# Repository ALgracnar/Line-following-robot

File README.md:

# Line-following-robot

Rečeno, storjeno. GitHub acount ustvarjen in KiCad naložen.
Lp, Aljaž Gračnar

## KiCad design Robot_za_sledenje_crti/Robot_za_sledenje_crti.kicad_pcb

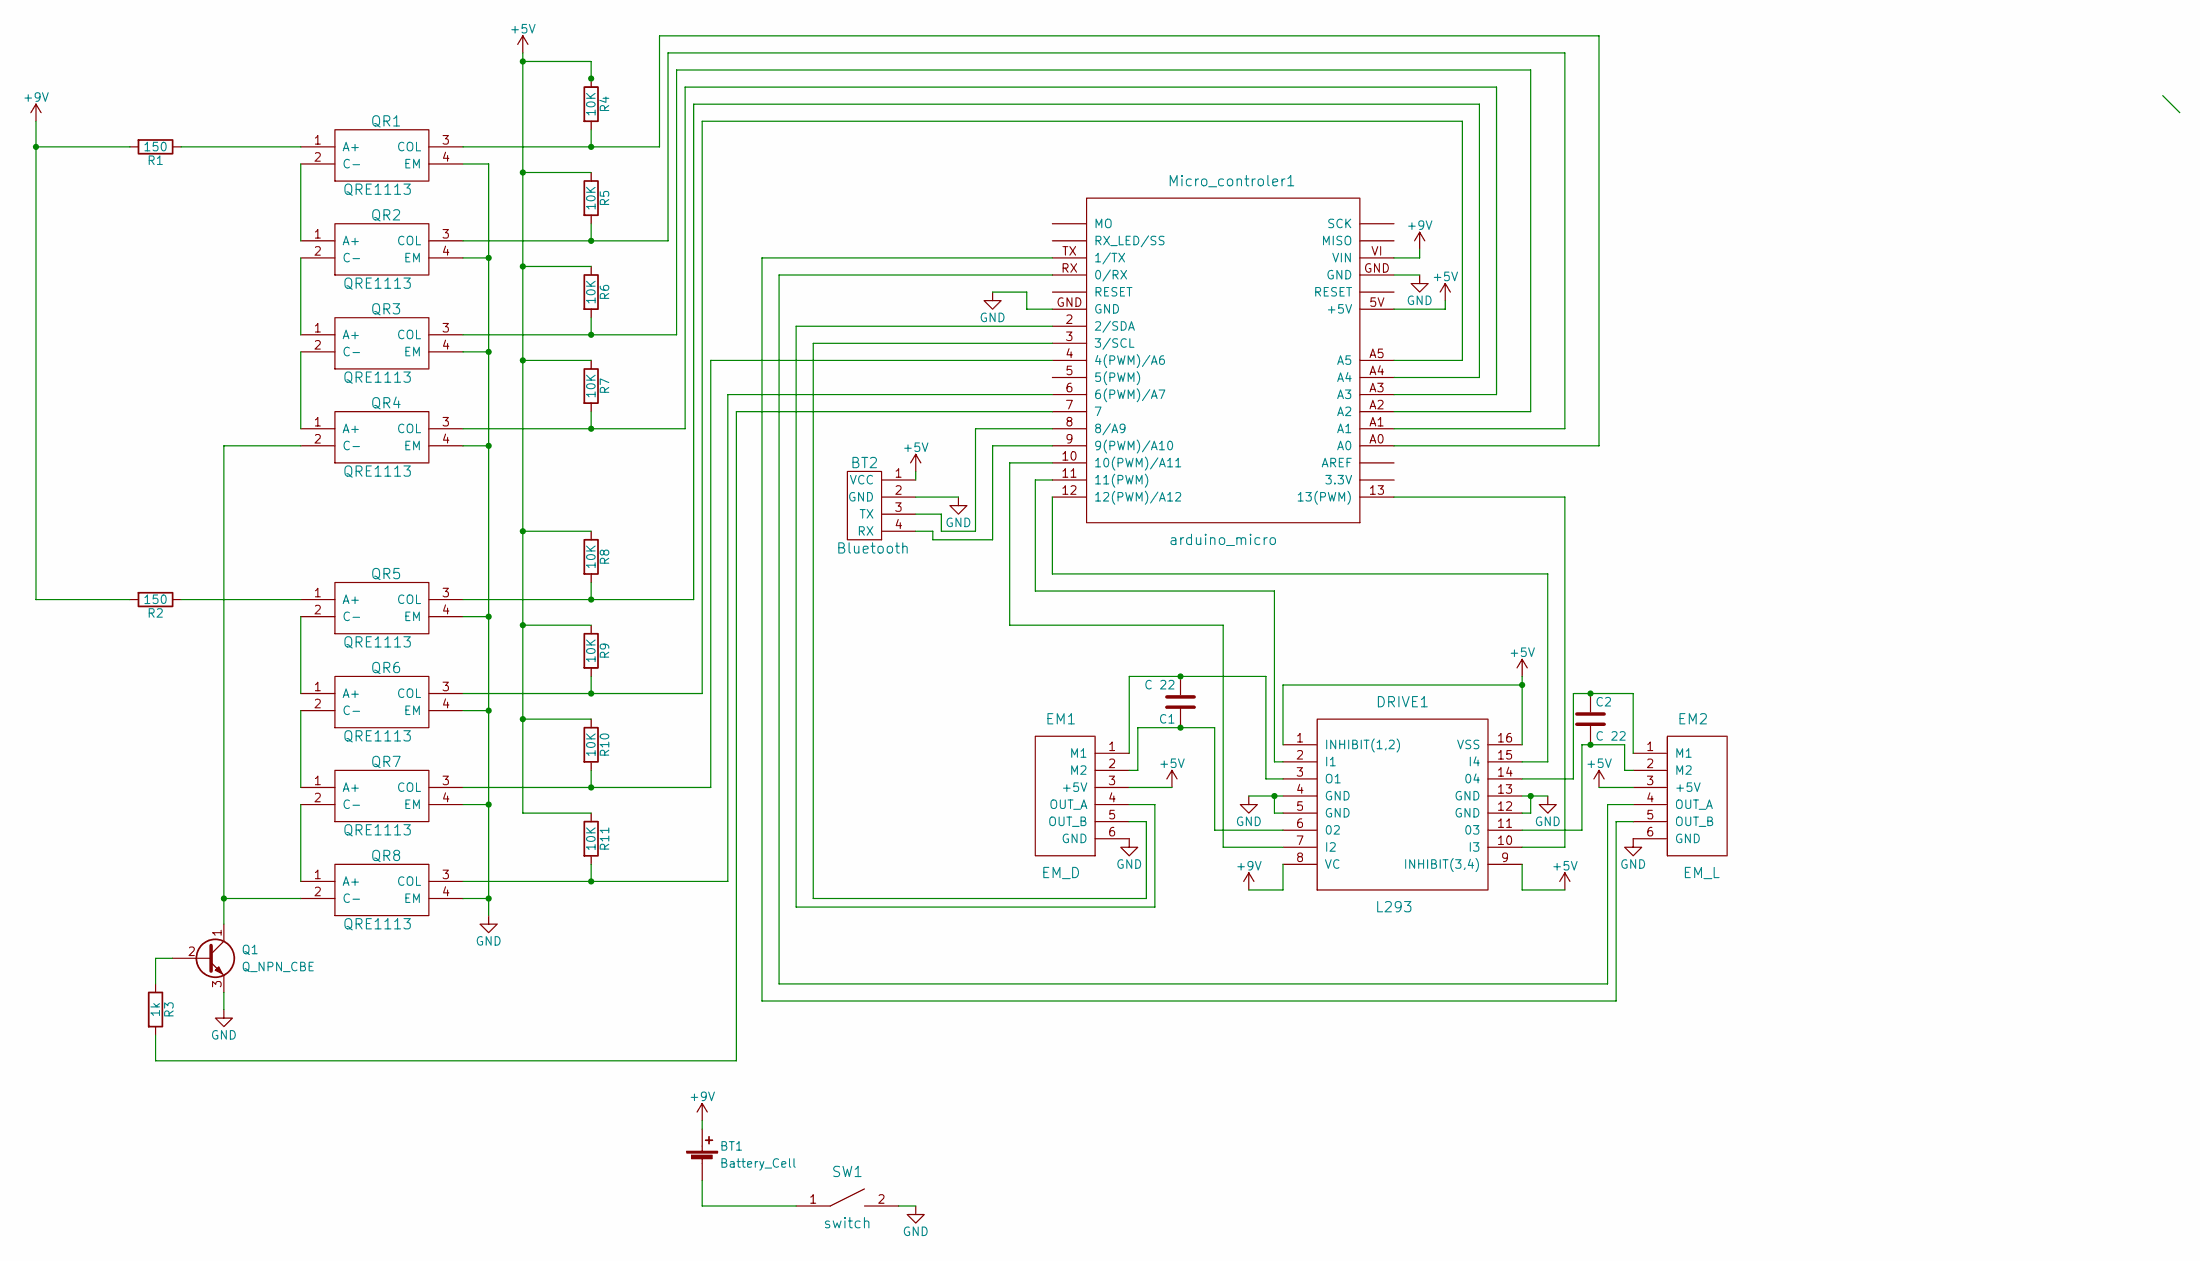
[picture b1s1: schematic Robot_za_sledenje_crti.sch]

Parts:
BT1: Battery_Cell; Baterry
BT2: Bluetooth; JY_MCU
C1, C2: C 22; C_0805_HandSoldering
DRIVE1: L293; L293DNE
EM1: EM_D; EM_Encoder
EM2: EM_L; EM_Encoder
Micro_controler1: arduino_micro; ARDUINO_MICRO_SHIELD
Q1: Q_NPN_CBE; BSV52_NPN
QR1, QR2, QR3, QR4, QR5, QR6, QR7, QR8: QRE1113; qre1113GR
R1, R2: 150; R_0805_HandSoldering
R3: 1k; R_0805_HandSoldering
R4, R5, R6, R7, R8, R9, R10, R11: 10K; R_0805_HandSoldering
SW1: switch

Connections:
+5V: BT2.1 (VCC), DRIVE1.1 (INHIBIT(1,2)), DRIVE1.9 (INHIBIT(3,4)), DRIVE1.16 (VSS), EM1.3 (+5V), EM2.3 (+5V), Micro_controler1.5V (+5V), R4.1, R5.1, R6.1, R7.1, R8.1, R9.1, R10.1, R11.1
+9V: BT1.1 (+), DRIVE1.8 (VC), Micro_controler1.VI (VIN), R1.2, R2.2
GND: BT2.2 (GND), DRIVE1.4 (GND), DRIVE1.5 (GND), DRIVE1.12 (GND), DRIVE1.13 (GND), EM1.6 (GND), EM2.6 (GND), Micro_controler1.GND, Q1.3 (E), QR1.4 (EM), QR2.4 (EM), QR3.4 (EM), QR4.4 (EM), QR5.4 (EM), QR6.4 (EM), QR7.4 (EM), QR8.4 (EM), SW1.2
unnamed: BT1.2 (-), SW1.1
unnamed: BT2.3 (TX), Micro_controler1.8 (8/A9)
unnamed: BT2.4 (RX), Micro_controler1.9 (9(PWM)/A10)
unnamed: C1.1, DRIVE1.6 (02), EM1.2 (M2)
unnamed: C1.2, DRIVE1.3 (O1), EM1.1 (M1)
unnamed: C2.1, DRIVE1.14 (04), EM2.1 (M1)
unnamed: C2.2, DRIVE1.11 (03), EM2.2 (M2)
unnamed: DRIVE1.2 (I1), Micro_controler1.11 (11(PWM))
unnamed: DRIVE1.7 (I2), Micro_controler1.10 (10(PWM)/A11)
unnamed: DRIVE1.10 (I3), Micro_controler1.13 (13(PWM))
unnamed: DRIVE1.15 (I4), Micro_controler1.12 (12(PWM)/A12)
unnamed: EM1.4 (OUT_A), Micro_controler1.2 (2/SDA)
unnamed: EM1.5 (OUT_B), Micro_controler1.3 (3/SCL)
unnamed: EM2.4 (OUT_A), Micro_controler1.RX (0/RX)
unnamed: EM2.5 (OUT_B), Micro_controler1.TX (1/TX)
unnamed: Micro_controler1.4 (4(PWM)/A6), QR7.3 (COL), R10.2
unnamed: Micro_controler1.6 (6(PWM)/A7), QR8.3 (COL), R11.2
unnamed: Micro_controler1.7, R3.2
unnamed: Micro_controler1.A0, QR1.3 (COL), R4.2
unnamed: Micro_controler1.A1, QR2.3 (COL), R5.2
unnamed: Micro_controler1.A2, QR3.3 (COL), R6.2
unnamed: Micro_controler1.A3, QR4.3 (COL), R7.2
unnamed: Micro_controler1.A4, QR5.3 (COL), R8.2
unnamed: Micro_controler1.A5, QR6.3 (COL), R9.2
unnamed: Q1.1 (C), QR4.2 (C-), QR8.2 (C-)
unnamed: Q1.2 (B), R3.1
unnamed: QR1.1 (A+), R1.1
unnamed: QR1.2 (C-), QR2.1 (A+)
unnamed: QR2.2 (C-), QR3.1 (A+)
unnamed: QR3.2 (C-), QR4.1 (A+)
unnamed: QR5.1 (A+), R2.1
unnamed: QR5.2 (C-), QR6.1 (A+)
unnamed: QR6.2 (C-), QR7.1 (A+)
unnamed: QR7.2 (C-), QR8.1 (A+)

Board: 2 copper layers, 30 parts (0 on the bottom side), 37 nets, no tracks yet.

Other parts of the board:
Ball: Ball caster; ballcaster
